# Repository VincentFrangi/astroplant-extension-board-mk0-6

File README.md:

# Astroplant Extension Board MK0.6

## About This Project

[Interactive BOM](http://htmlpreview.github.io/?https://github.com/VincentFrangi/astroplant-extension-board-mk0-6/blob/master/ibom.html)

## Renderings

### Top

### Bottom

## BOM

|Count|Component|Details|Datasheet|
|-|-|-|-|
|2x|C1 / C2|CAP CER 0.1UF 25V X7R 0805|[Link](http://datasheets.avx.com/X7RDielectric.pdf)|
|1x|C4|CAP ALUM POLY 470UF 20% 25V SMD|[Link](https://industrial.panasonic.com/cdbs/www-data/pdf/RDD0000/ABA0000C1229.pdf)|
|1x|C3|CAP ALUM POLY 470UF 20% 6.3V SMD|[Link](https://katalog.we-online.de/pbs/datasheet/875115150005.pdf)|
|1x|D1|LED BLUE ESS II SMD|[Link](https://industrial.panasonic.com/content/data/SC/ds/ds4/LNJ937W8CRA_E.pdf)|
|3x|D2 / D3 / D4|DIODE GEN PURP 50V 1A SMA|[Link](http://www.smc-diodes.com/propdf/S1A-S1M%20N0560%20REV.B.pdf)|
|1x|D5|LED AMBER ESS II SMD|[Link](https://industrial.panasonic.com/content/data/SC/ds/ds4/LNJ437W84RA_E.pdf)|
|1x|J1|CONN HEADER XH TOP 6POS 2.5MM|[Link](http://www.jst-mfg.com/product/pdf/eng/eXH.pdf)|
|9x|J10 / J12 / J22 / J23 / J24 / J25 / J26 / J27 / J6|CONN HEADER XH TOP 4POS 2.5MM|[Link](http://www.jst-mfg.com/product/pdf/eng/eXH.pdf)|
|1x|J2|CONN HEADER VERT 40POS 2.54|[Link](http://katalog.we-online.de/em/datasheet/6130xx21121.pdf)|
|2x|J20 / J21|TERM BLOCK 5.08MM VERT 2POS PCB|[Link](http://www.on-shore.com/wp-content/uploads/2015/09/OSTTAXX4163.pdf)|
|7x|J11 / J16 / J17 / J18 / J19 / J5 / J8|CONN HEADER XH TOP 2POS 2.5MM|[Link](http://www.jst-mfg.com/product/pdf/eng/eXH.pdf)|
|4x|J3 / J4 / J7 / J9|CONN HEADER XH TOP 3POS 2.5MM|[Link](http://www.jst-mfg.com/product/pdf/eng/eXH.pdf)|
|1x|JP1|CONN HEADER 3 POS 2.54|[Link](http://katalog.we-online.de/em/datasheet/6130xx11121.pdf)|
|1x|JP2|CONN HEADER 2 POS 2.54|[Link](http://katalog.we-online.de/em/datasheet/6130xx11121.pdf)|
|5x|Q1 / Q2 / Q3 / Q4 / Q5|MOSFET N-CH 30V 5A SOT23|[Link](http://www.infineon.com/dgdl/irlml6344pbf.pdf?fileId=5546d462533600a4015356689c44262c)|
|1x|R11|RES SMD 180 OHM 5% 0.4W 0805|[Link](https://www.rohm.com/datasheet/ESR01MZPF/esr-e)|
|1x|R6|RES SMD 27 OHM 0.5% 1/16W 0603|[Link](http://www.susumu.co.jp/common/pdf/n_catalog_partition05_en.pdf)|
|6x|R1 / R2 / R3 / R4 / R5 / R7|RES SMD 10K OHM 0.5% 1/10W 0805|[Link](http://www.susumu.co.jp/common/pdf/n_catalog_partition05_en.pdf)|
|3x|R10 / R8 / R9|RES SMD 100K OHM 0.1% 1/8W 0805|[Link](http://www.susumu.co.jp/common/pdf/n_catalog_partition01_en.pdf)|
|3x|SW1 / SW2 / SW3|SWITCH TACTILE SPST-NO 0.02A 15V|[Link](https://www3.panasonic.biz/ac/e_download/control/switch/light-touch/catalog/sw_lt_eng_5n.pdf)|

---

This project is managed and available on

You can view it [here](https://aisler.net/p/DBKSBTQF). Start your own Powerful Prototype on [here](https://aisler.net).

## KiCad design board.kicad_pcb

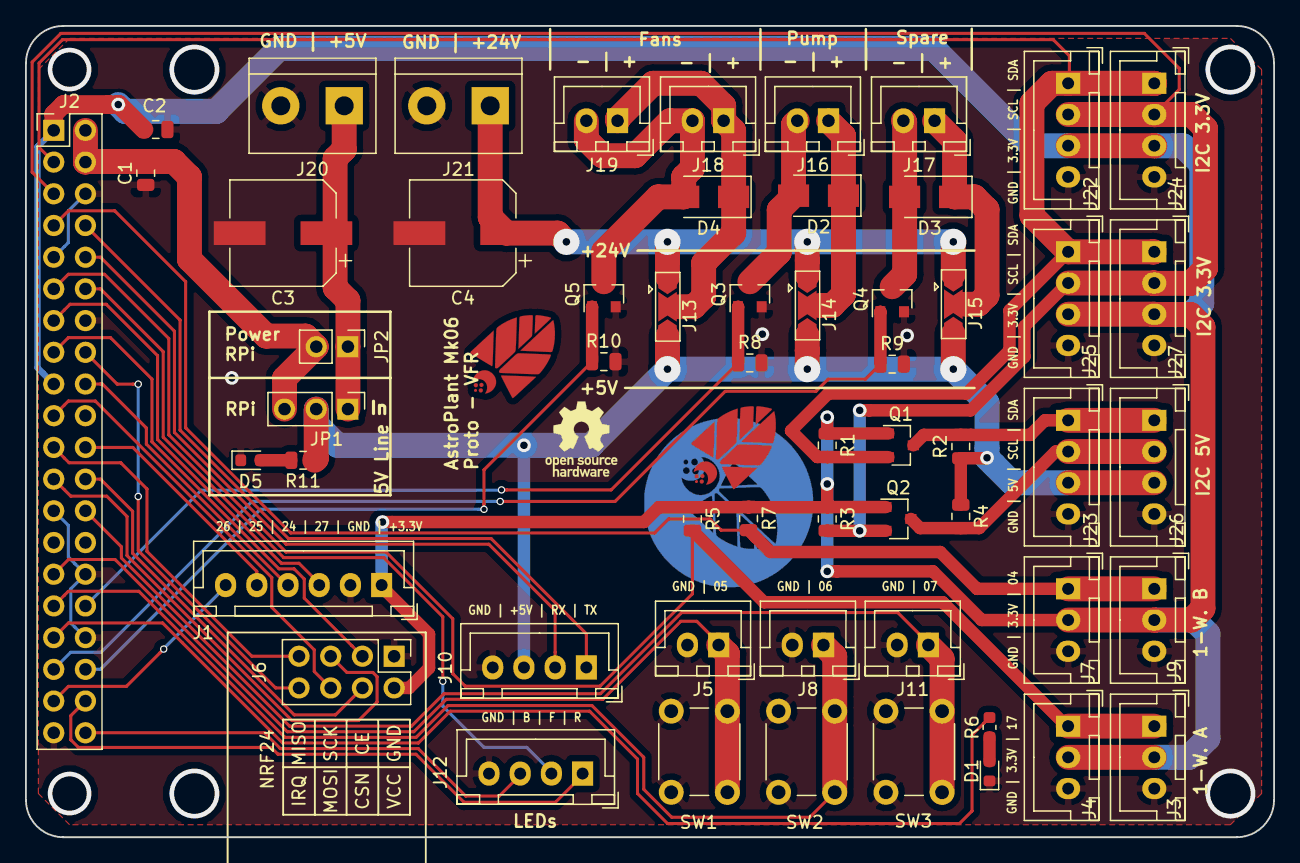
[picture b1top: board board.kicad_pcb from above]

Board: 2 copper layers, 100.0 x 65.0 mm, 57 parts (0 on the bottom side), 42 nets.

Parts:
C1, C2: 0.1uF; C_0805_2012Metric
C3: 470uF; CP_Elec_8x6.9
C4: 470u; CP_Elec_8x11.9
D1: LED_Blue; LED_0603_1608Metric
D2, D3, D4: S1A; D_SMA
D5: LED_Amber; LED_0603_1608Metric
J1: JST_XH_Relays; JST_XH_B06B-XH-A_1x06_P2.50mm_Vertical
J2: 2x40 2.5mm Header; Pin_Header_Straight_2x20_Pitch2.54mm
J3, J4, J7, J9: JST-XH_3; JST_XH_B03B-XH-A_1x03_P2.50mm_Vertical
J5, J8, J11, J16, J17, J18, J19: JST_HX_2; JST_XH_B02B-XH-A_1x02_P2.50mm_Vertical
J6: Conn_02x04_Odd_Even; Pin_Header_Straight_2x04_Pitch2.54mm
J10: JST_XH_UART; JST_XH_B04B-XH-A_1x04_P2.50mm_Vertical
J12: JST-XH_LED_GND; JST_XH_B04B-XH-A_1x04_P2.50mm_Vertical
J13, J14, J15: GS3; SolderJumper-3_P2.0mm_Open_TrianglePad1.0x1.5mm
J20, J21: Conn_01x02; TerminalBlock_bornier-2_P5.08mm
J22, J23, J24, J25, J26, J27: JST_XH_I2C; JST_XH_B04B-XH-A_1x04_P2.50mm_Vertical
JP1: Jumper_3_Bridged12; PinHeader_1x03_P2.54mm_Vertical
JP2: Jumper_2_Bridged; PinHeader_1x02_P2.54mm_Vertical
Q1, Q2, Q3, Q4, Q5: IRLML6344TRPBF; SOT-23
R1, R2, R3, R4, R5, R7: 10K; R_0805_2012Metric
R6: 27; R_0603_1608Metric
R8, R9, R10: 100K; R_0805_2012Metric
R11: 180; R_0805_2012Metric
SW1, SW2, SW3: SW_Push; SW_PUSH_6mm

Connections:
5V_IN: C3.1, J20.1, JP1.1, JP2.1
5V_RPi: C1.2, J2.2, J2.4, JP1.3, JP2.2
+3V3: C2.2, J1.1, J2.1, J2.17, J3.2, J4.2, J6.2, J7.2, J9.2, J22.3, J24.3, J25.3, J27.3, Q1.1, Q2.1, R1.1, R3.1, R5.1, R7.1
+5V: J10.3, J13.3, J14.3, J15.3, J23.3, J26.3, JP1.2, R2.1, R4.1, R11.1
+24V: C4.1, J13.1, J14.1, J15.1, J21.1
CE0: J2.24, J6.4
GND: C1.1, C2.1, C3.2, C4.2, D1.1, D5.1, J1.2, J2.6, J2.9, J2.14, J2.20, J2.25, J2.30, J2.34, J2.39, J3.3, J4.3, J5.2, J6.1, J7.3, J8.2, J9.3, J10.4, J11.2, J12.4, J20.2, J21.2, J22.4, J23.4, J24.4, J25.4, J26.4, J27.4, Q3.2, Q4.2, Q5.2, R8.2, R9.2, R10.2, SW1.2, SW2.2, SW3.2
GPIO4: J2.7, J7.1, J9.1, R7.2
GPIO5: J2.29, J5.1, SW1.1
GPIO6: J2.31, J8.1, SW2.1
GPIO7: J2.26, J11.1, SW3.1
GPIO12: J2.32, Q3.1, R8.1
GPIO13: J2.33, R6.1
GPIO16: J2.36, Q5.1, R10.1
GPIO17: J2.11, J3.1, J4.1, R5.2
GPIO18: J2.12, J12.2
GPIO19: J2.35, Q4.1, R9.1
GPIO20: J2.38, J12.1
GPIO21: J2.40, J12.3
GPIO22: J2.15, J6.3
GPIO23: J2.16, J6.8
GPIO24: J1.4, J2.18
GPIO25: J1.5, J2.22
GPIO26: J1.6, J2.37
GPIO27: J1.3, J2.13
MISO: J2.21, J6.7
MOSI: J2.19, J6.6
unnamed: D1.2, R6.2
unnamed: D2.1, J14.2, J16.1
unnamed: D2.2, J16.2, Q3.3
unnamed: D3.1, J15.2, J17.1
unnamed: D3.2, J17.2, Q4.3
unnamed: D4.1, J13.2, J18.1, J19.1
unnamed: D4.2, J18.2, J19.2, Q5.3
unnamed: D5.2, R11.2
RX: J2.10, J10.2
SCL: J2.5, J22.2, J24.2, J25.2, J27.2, Q2.2, R3.2
SCLK: J2.23, J6.5
SCL_5V: J23.2, J26.2, Q2.3, R4.2
SDA: J2.3, J22.1, J24.1, J25.1, J27.1, Q1.2, R1.2
SDA_5V: J23.1, J26.1, Q1.3, R2.2
TX: J2.8, J10.1

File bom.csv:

Count,Component,Details,Datasheet
2x,"C1 / C2","CAP CER 0.1UF 25V X7R 0805","http://datasheets.avx.com/X7RDielectric.pdf"
1x,"C4","CAP ALUM POLY 470UF 20% 25V SMD","https://industrial.panasonic.com/cdbs/www-data/pdf/RDD0000/A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"
1x,"C3","CAP ALUM POLY 470UF 20% 6.3V SMD","https://katalog.we-online.de/pbs/datasheet/875115150005.pdf"
1x,"D1","LED BLUE ESS II SMD","https://industrial.panasonic.com/content/data/SC/ds/ds4/LNJ9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"
3x,"D2 / D3 / D4","DIODE GEN PURP 50V 1A SMA","http://www.smc-diodes.com/propdf/S1A-S1M%20N0560%20REV.B.pdf"
1x,"D5","LED AMBER ESS II SMD","https://industrial.panasonic.com/content/data/SC/ds/ds4/LNJ4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"
1x,"J1","CONN HEADER XH TOP 6POS 2.5MM","http://www.jst-mfg.com/product/pdf/eng/eXH.pdf"
9x,"J10 / J12 / J22 / J23 / J24 / J25 / J26 / J27 / J6","CONN HEADER XH TOP 4POS 2.5MM","http://www.jst-mfg.com/product/pdf/eng/eXH.pdf"
1x,"J2","CONN HEADER VERT 40POS 2.54","http://katalog.we-online.de/em/datasheet/6130xx21121.pdf"
2x,"J20 / J21","TERM BLOCK 5.08MM VERT 2POS PCB","http://www.on-shore.com/wp-content/uploads/2015/09/OSTTAXX4163.pdf"
7x,"J11 / J16 / J17 / J18 / J19 / J5 / J8","CONN HEADER XH TOP 2POS 2.5MM","http://www.jst-mfg.com/product/pdf/eng/eXH.pdf"
4x,"J3 / J4 / J7 / J9","CONN HEADER XH TOP 3POS 2.5MM","http://www.jst-mfg.com/product/pdf/eng/eXH.pdf"
1x,"JP1","CONN HEADER 3 POS 2.54","http://katalog.we-online.de/em/datasheet/6130xx11121.pdf"
1x,"JP2","CONN HEADER 2 POS 2.54","http://katalog.we-online.de/em/datasheet/6130xx11121.pdf"
5x,"Q1 / Q2 / Q3 / Q4 / Q5","MOSFET N-CH 30V 5A SOT23","http://www.infineon.com/dgdl/irlml6344pbf.pdf?fileId=5546d46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"
1x,"R11","RES SMD 180 OHM 5% 0.4W 0805","https://www.rohm.com/datasheet/ESR01MZPF/esr-e"
1x,"R6","RES SMD 27 OHM 0.5% 1/16W 0603","http://www.susumu.co.jp/common/pdf/n_catalog_partition05_en.pdf"
6x,"R1 / R2 / R3 / R4 / R5 / R7","RES SMD 10K OHM 0.5% 1/10W 0805","http://www.susumu.co.jp/common/pdf/n_catalog_partition05_en.pdf"
3x,"R10 / R8 / R9","RES SMD 100K OHM 0.1% 1/8W 0805","http://www.susumu.co.jp/common/pdf/n_catalog_partition01_en.pdf"
3x,"SW1 / SW2 / SW3","SWITCH TACTILE SPST-NO 0.02A 15V","https://www3.panasonic.biz/ac/e_download/control/switch/ligh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"

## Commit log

2018-09-21 Syncing AISLER project with GitHub repository
2018-10-08 Addd schematics and production files
2018-11-08 add 3d model
2018-11-15 Add interactiv BOM
2018-11-15 Add link to interactive BOM
2018-11-16 Add front Mask
2018-11-19 Add bottom mask
2018-11-27 Add position files
